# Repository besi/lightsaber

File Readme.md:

# Lightsaber

This is my lightsaber featuring a custom made PCB and as Neopixel strip.

## Pinout of the wemos c3 pico

| Function          | Pin |
|-------------------|----:|
| Neopixelstrip     |   2 |
| Mode button       |   5 |
| Internal RGB*     |   7 |
| Potentiometer     |   1 |
| Batteryvoltage**  |   3 |

\* This is a GRB instead of RGB LED  
\** This requires a solder jumper on the back of the C3 board

## Credits

- 3D model of the 18650 battery by John Michael Loeffler

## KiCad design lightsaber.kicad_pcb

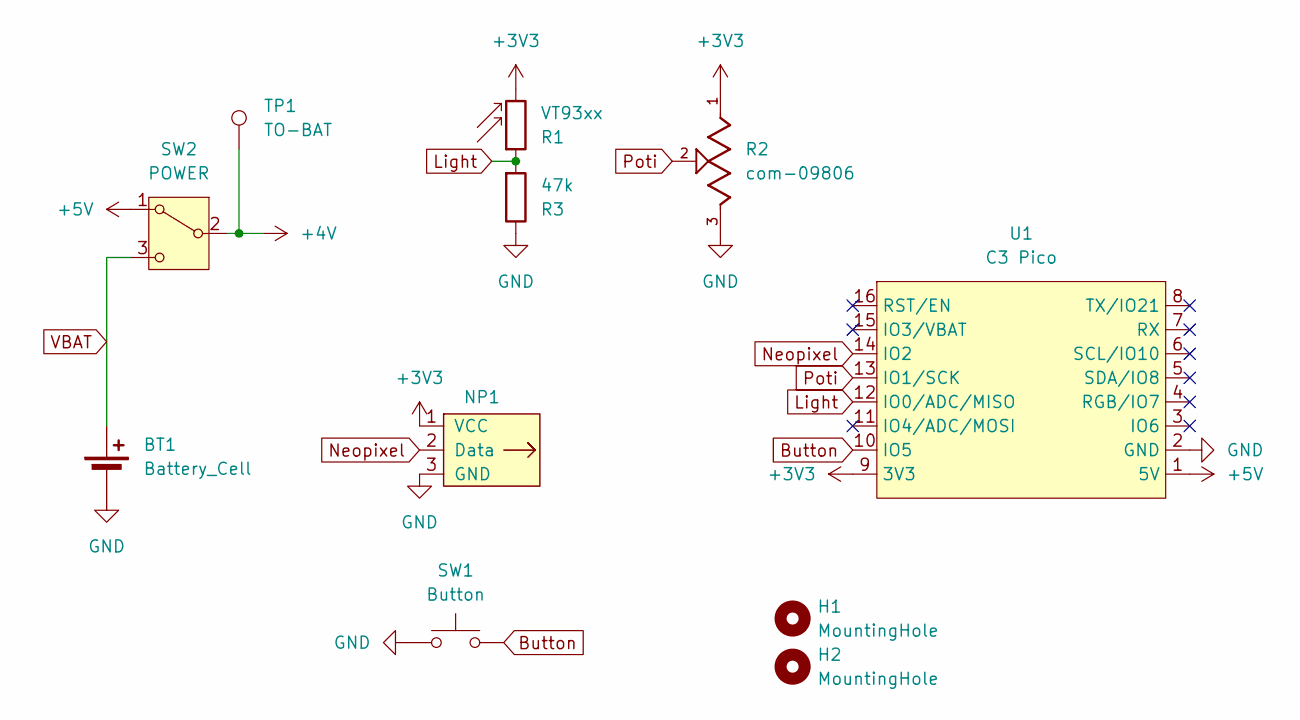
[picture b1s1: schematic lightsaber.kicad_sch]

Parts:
BT1: Battery_Cell; BatteryHolder_MPD_BH-18650-PC2
H1, H2: MountingHole; MountingHole_3.2mm_M3
NP1: LEDs_Out; neopixel-strip
R1: VT93xx; R_LDR_5.1x4.3mm_P3.4mm_Vertical
R2: com-09806
R3: 47k; R_0805_2012Metric_Pad1.20x1.40mm_HandSolder
SW1: Button; pts636
SW2: POWER; SW_SPDT_CK_JS102011SAQN
TP1: TO-BAT; TestPoint_Loop_D2.50mm_Drill1.0mm
U1: C3 Pico; c3-pico

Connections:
+3V3: NP1.1 (VCC), R1.2, R2.1, U1.9 (3V3)
+4V: SW2.2 (B), TP1.1
+5V: SW2.1 (A), U1.1 (5V)
Button: SW1.2, U1.10 (IO5)
GND: BT1.2 (-), NP1.3 (GND), R2.3, R3.1, SW1.1, U1.2 (GND)
Light: R1.1, R3.2, U1.12 (IO0/ADC/MISO)
Neopixel: NP1.2 (Data), U1.14 (IO2)
Poti: R2.2, U1.13 (IO1/SCK)
VBAT: BT1.1 (+), SW2.3 (C)

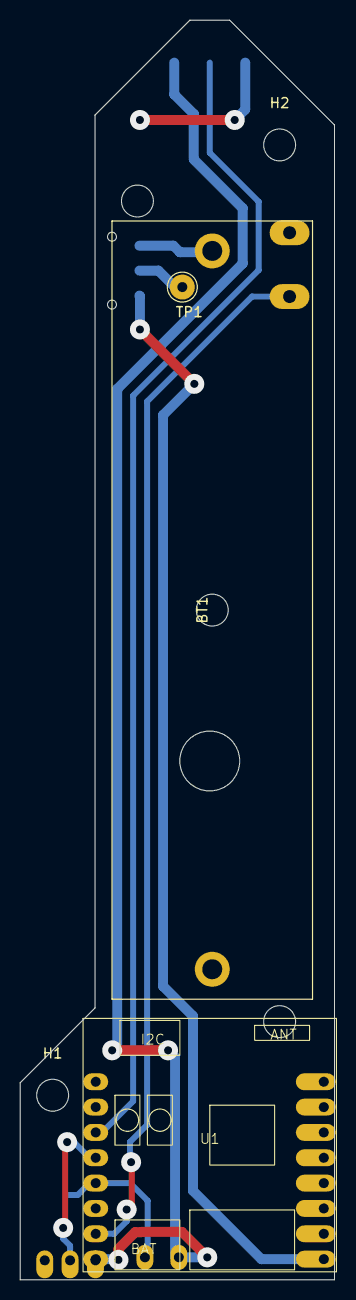
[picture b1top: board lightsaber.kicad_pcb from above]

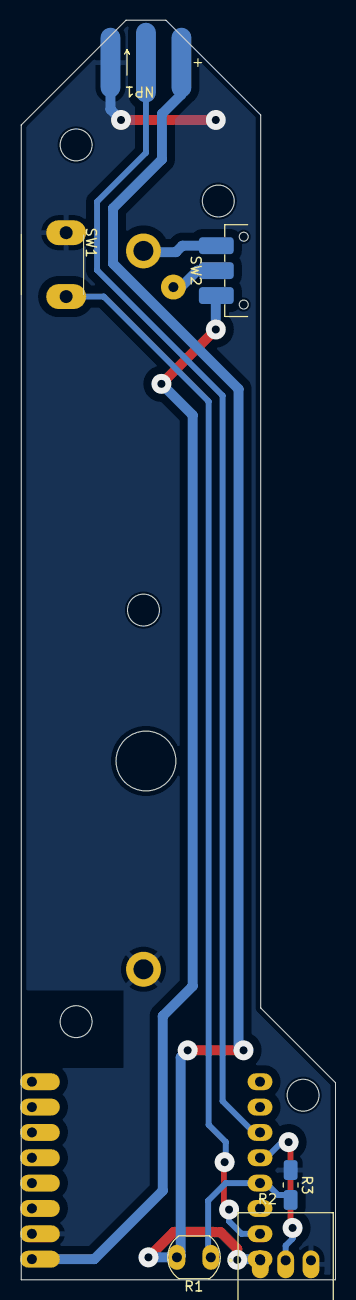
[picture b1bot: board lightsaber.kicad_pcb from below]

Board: 2 copper layers, 31.5 x 126.2 mm, 11 parts (6 on the bottom side), 9 nets.

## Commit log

2025-12-10 Initial commit with various footprints
2025-12-10 Update c3 pico library
2025-12-10 Preliminary PCB layout
2025-12-10 Add grid origin for step export
2025-12-11 Update neopixel library
2025-12-11 Update PCB for Lightsaber
2025-12-11 Fixed switch between 5V and V_Batt
2025-12-11 Fix edge component placements
2025-12-11 Add light saber software
2025-12-11 Manage the last and current color
2025-12-11 Add white
2025-12-11 Don't checkin the step file
2025-12-11 Make sure that the neopixel does not drain the battery so use 3V3 instead of VBAT
2025-12-12 Adjust the brightness according to the potentiometer's position
2025-12-13 Specify light sensor and its resistor
2025-12-15 Change pinout, add m3 mounting holes
2025-12-15 Cleanup pcb
2025-12-15 Add Readme.md and stl files
2025-12-15 Fix pin 5 does not allow ADC
2025-12-15 Fix pin mapping - WARNING the old hardware has different pins assigned
2025-12-15 Reverse the polarity of the slide switch
2025-12-16 Denote the ADC pins
    And change the pinout for the light sensor
2025-12-16 Add pinout to Readme
2025-12-16 Add credits and description to the Readme
2025-12-16 Allow changing the brightness while the color is shown
2025-12-16 Allow two different hardware models
2025-12-16 balance colors
2025-12-16 increase dim factor
2025-12-16 Ambient light sensor does not work
    opens #1
2025-12-16 Add space for github new line
2025-12-21 Display the bath tub temperature when the button is pressed during startup
2025-12-21 Code re-work
